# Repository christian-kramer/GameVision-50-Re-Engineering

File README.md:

# GameVision-50-Re-Engineering
Turning a bizarre Russian/Taiwanese NES clone into something useful.
___

I've been definitely been looking in strange places for personal projects to do, lately. During my search I stumbled upon an old all-in-one game console/controller I used to play with when I was young.

This project is a continuation and implementation of my [STM32F103C8T6-Familiarization repo](https://github.com/christian-kramer/STM32F103C8T6-Familiarization)

It's called the **GameVision 50**, presumably because it has 50 games.

Here is the full list of games, in case anyone recognizes one.

And, as an example, here's "Truck Race":

The games aren't exactly sophisticated... not quite the level of immersion I'm looking for. The wheel is nice, though. I wonder how hard it would be to adapt it for use with a PC?

Let's open it up and have a look.

Seems a lot less complicated than I thought it would be, actually. Let's take a closer look at that mainboard.

Interesting layout, for sure. The big chip on the right is almost certainly a parallel flash IC, the chip-on-board in the lower-left is probably the main game processor (more on that in a bit), and quite honestly I have no idea what the "chip-on-board, on-board" thing in the top left is. It's gotta be a coprocessor of some sort, because it's thoroughly interconnected with both the game chip, and the flash chip. A converter between parallel flash and whatever interface the game processor requires, perhaps?

I'm interested in that connector on the far right of the board. It definitely doesn't appear to be a multiplexed analog button arrangement... the pin names like "SCK1", "OUT0", and "VCC" seem to indicate we've got some other device at the other end of this cable speaking a serial data language. I have never heard of "OUT0" in any serial data protocol I've worked with.

I googled some of these pinout names, and the first result on Google was [this webpage](http://xn----ctbgeuhdtdb2b.xn--p1ai/price/dendy/?parts&d=DW-MH-3):

Woah! That's a lot of Russian. I can read some Russian, but not stuff that's this technical.

That's better. Looks like it's actually pretty straightforward. Dendy DW-MH-3? I've never heard of the company "Dendy Processors" before. I really want to know more about this chip.

Googling the company "Dendy Processors" led me to this Wikipedia page:

Holy cow! "Dendy" was actually a Soviet NES clone! This project just got *really* interesting. I guess technically now I'm reverse-engineering 80's-vintage Soviet tech.

This makes a lot of sense now, because studying the board more I notice the oscillator's frequency is very familiar:

The frequency indicated on this oscillator is 21.4772 MHz... Check out what we get when we google this frequency.

It's all NES/SNES stuff! Ha!

That last link is interesting, too. The *reason* 21.4772 MHz is used is because that's the sample rate for 525-line B-MAC video encoding.

70's/80's video encoding standards are absolutely fascinating, and I highly encourage you to explore this rabbit hole if you're interested. The Wikipedia article on B-MAC  is a great starting point with tons of links that will take you further.

Back to the project at hand! The Russian Dendy documentation page indicates VCC gets +5v, OUT0 is a common clock, SCK1 and SCK2 are clocks specific to each controller, and P1D0/P2D0 are the lines that the controllers transmit data on.

I've got a logic analyzer I can hook up to this and see if I can recognize a pattern.

Next, let's fire it up and press some buttons!

The top line is SCK1, and the next line down is P1D0. Looks like we've got a 2-byte "packet" clocked out by SCK1, with a little bit of a pause separating them. I'm curious, though... The webpage mentioned that OUT0 is a "common clock"... What does its output look like?

Ah, okay! OUT0 appears to delineate each byte. It also looks like no matter which button I press on the wheel, both bytes are identical. I wonder if this is some crude error-checking going on?

Also, interestingly enough, this output is from the wheel being turned all the way to the left, meaning that although there's a potentiometer attached to the steering column, there is no analog data coming back to the Dendy chip... turning the wheel is functionally equivalent to pressing the left or right d-pad buttons! This will need to be rewired if we want this to function as an analog axis.

At this point, I think I'm comfortable enough with the Dendy controller protocol to try hooking this up to an STM32 Blue Pill.

What you see here is the steering wheel controller of the GameVision 50 bypassing the original mainboard and communicating entirely with the STM32. Interestingly, it's able to interface directly with the STM32 without level-shifting because STM32 inputs are 5v tolerant, and 3.3v is above the TTL "logic high" threshold. The potentiometer on the breadboard is a stand-in for the one that's built-in to the steering column. I'll use that potentiometer in the final version.

After I got it talking with my PC and being recognized as a "Game Pad" in Windows with a single "steering" axis, it was time to take this rat's nest of wiring and turn it into a PCB!

I decided to keep the same shape and general layout as the original mainboard so that it may be a drop-in replacement/conversion. It felt much more professional, that way. Additionally, I broke out the steering wheel connector into test-points so that I may easily connect my logic analyzer in the event that I needed to debug my firmware in the future. The header for that is labeled J4, to the left of J5: the controller connector.

When the boards finally arrived, I was ecstatic about how they turned out! The "Gamevision" logo looks amazing, and all of the tiny capacitors and resistors were soldered perfectly. I opted to have the surface-mount components assembled at the factory due to the amount of fine-pitch soldering I would otherwise have to do myself. The only surface-mount component the factory couldn't do was the USB port, which was easy enough for me to hand-solder.

Here you can see my board (left) vs. the old board (right). You can see how similar they are physically, but it also really gives you an idea of just how much more component-dense the old board is compared to mine. Lots of analog signals going on over there!

Here's another comparison view showing how I incorporated the existing JST-XH-7 connector into my design. Because I retained the same connector in the same location, the wheel plugs right in like it was made for it!

Now, to tackle this empty shell. That potentiometer in the middle will need to be reworked in order to work the way I want it to. Let's take a closer look to see why.

Right now there's a big ol' glob of solder connecting the wiper pin with ground, making the potentiometer act like a variable resistor. This is then hooked up to the wheel's control board, which senses if the wheel is turned left or right, and registers a "left" or "right" button-press accordingly.

This doesn't work for what we want it to do! We want to measure *how far* the wheel is turned left or right, not "if". For that, we need to connect this potentiometer up to the  PCB directly so the STM32 can read the analog signal, and not the wheel. But, if we disconnect the potentiometer from the two wires and just leave them hanging, we'll forever get a "right" button press due to the infinite resistance!

We need to trick the wheel into thinking the potentiometer is always in the center. I measured 4.7KΩ across the potentiometer in the "center" positon, so an approximately 4.7KΩ fixed resistor soldered to the wires should be a perfect stand-in.

I had this resistor sitting in my "loose parts" bowl on my workbench. It measured something like 3.7KΩ, so close enough. After I soldered it on... no more "right" button press coming from the controller!

Lastly, here it is all assembled. I repurposed the 3-wire Audio/Video ribbon cable for the potentiometer, and it all works great! Steering is super smooth, and all of the buttons work!

I'm glad I incorporated the test-point pin header, next to the controller connector. Initially, during writing the firmware, I was getting some weird data I had never encountered before. When I pressed a button, my PC indicated many other buttons being pressed as well! To me, this looked like a timing issue... But I wasn't entirely sure where in my program the issue could be. Being able to easily connect a logic analyzer to inspect my signals allowed me to easily pinpoint the issue of "**P1D0**" not being pulled back up to +5V! This "floating" appeared as additional button presses to the STM32. Enabling the STM32's internal pull-up resistor on that pin in software allowed me to fix the issue without even needing a hardware fix.

After that, I closed it up and loaded up some games to try it out with!

Here is a video of me showing the wheel in action, playing Euro Truck Simulator 2:

[https://i.imgur.com/FMJOuTz.mp4](https://i.imgur.com/FMJOuTz.mp4)

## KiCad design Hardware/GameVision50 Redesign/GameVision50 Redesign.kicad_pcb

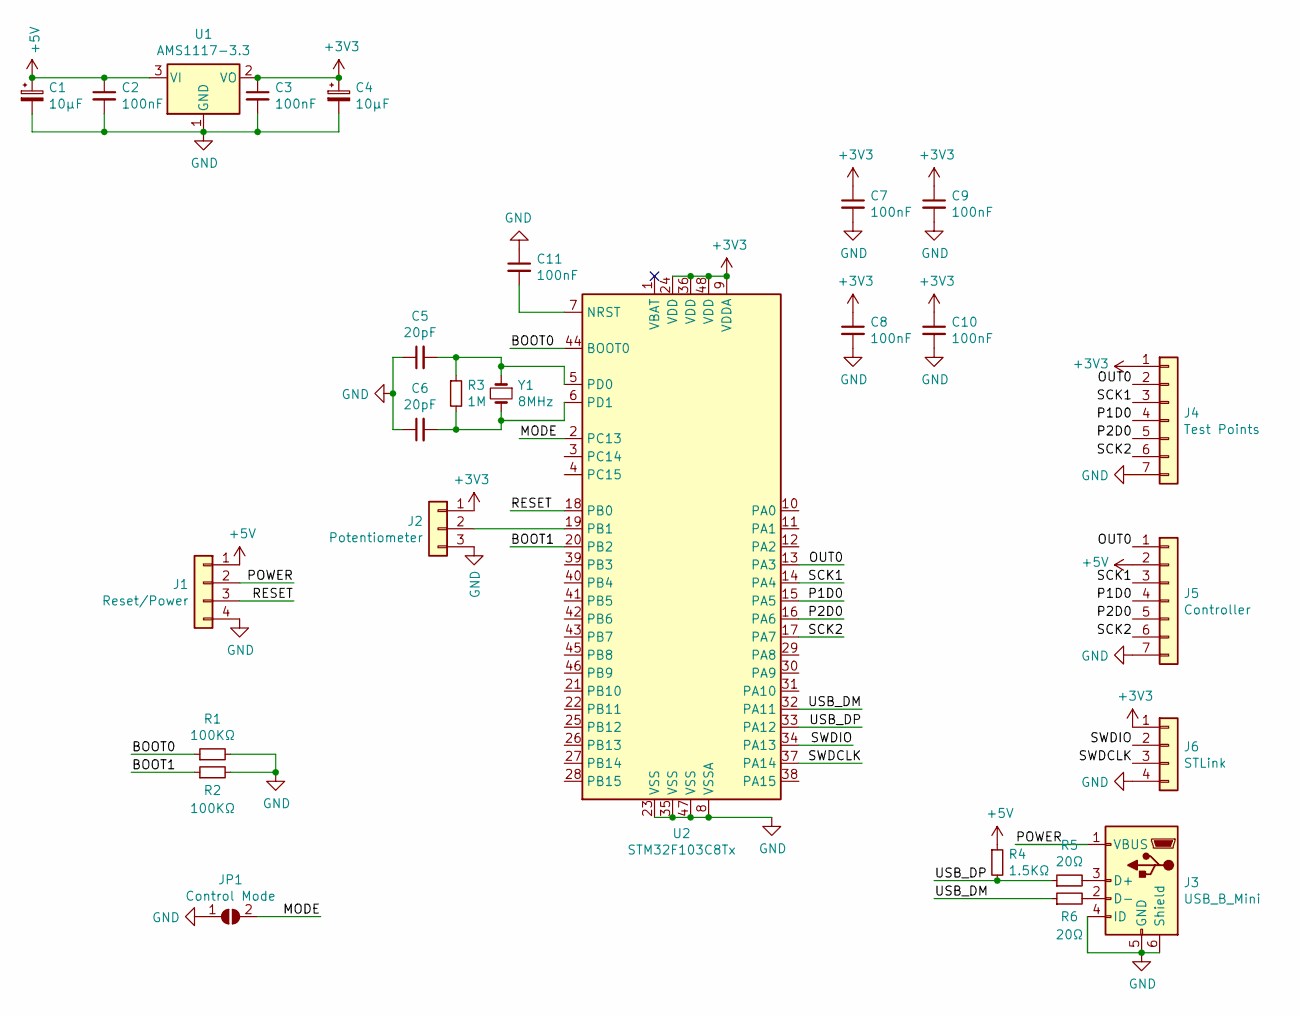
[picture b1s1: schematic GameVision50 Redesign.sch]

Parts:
C1, C4: 10μF; C_0805_2012Metric; LCSC C15850
C2, C3, C7, C8, C9, C10, C11: 100nF; C_0402_1005Metric; LCSC C1525
C5, C6: 20pF; C_0603_1608Metric; LCSC C1648
J1: Reset/Power; PinHeader_1x04_P2.54mm_Vertical
J2: Potentiometer; PinHeader_1x03_P2.54mm_Vertical
J3: USB_B_Mini; USB_Mini-B_Lumberg_2486_01_Horizontal
J4: Test Points; PinHeader_1x07_P2.54mm_Vertical
J5: Controller; JST_XH_B7B-XH-A_1x07_P2.50mm_Vertical
J6: STLink; PinHeader_1x04_P2.54mm_Vertical
JP1: Control Mode; SolderJumper-2_P1.3mm_Open_TrianglePad1.0x1.5mm
R1, R2: 100KΩ; R_0402_1005Metric; LCSC C25741
R3: 1M; R_0402_1005Metric; LCSC C26083
R4: 1.5KΩ; R_0402_1005Metric; LCSC C25867
R5, R6: 20Ω; R_0603_1608Metric; LCSC C22950
U1: AMS1117-3.3; SOT-223-3_TabPin2; LCSC C6186
U2: STM32F103C8Tx; LQFP-48_7x7mm_P0.5mm; LCSC C8734
Y1: 8MHz; Crystal_SMD_5032-2Pin_5.0x3.2mm; LCSC C115962

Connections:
+3V3: C3.1, C4.1, C7.1, C8.1, C9.1, C10.1, J2.1, J4.1, J6.1, U1.2 (VO), U2.9 (VDDA), U2.24 (VDD), U2.36 (VDD), U2.48 (VDD)
+5V: C1.1, C2.1, J1.1, J5.2, R4.1, U1.3 (VI)
/BOOT0: R1.1, U2.44 (BOOT0)
/BOOT1: R2.1, U2.20 (PB2)
/MODE: JP1.2 (B), U2.2 (PC13)
/OUT0: J4.2, J5.1, U2.13 (PA3)
/P1D0: J4.4, J5.4, U2.15 (PA5)
/P2D0: J4.5, J5.5, U2.16 (PA6)
/POWER: J1.2, J3.1 (VBUS)
/RESET: J1.3, U2.18 (PB0)
/SCK1: J4.3, J5.3, U2.14 (PA4)
/SCK2: J4.6, J5.6, U2.17 (PA7)
/SWDCLK: J6.3, U2.37 (PA14)
/SWDIO: J6.2, U2.34 (PA13)
/USB_DM: R6.1, U2.32 (PA11)
/USB_DP: R4.2, R5.1, U2.33 (PA12)
GND: C1.2, C2.2, C3.2, C4.2, C5.1, C6.1, C7.2, C8.2, C9.2, C10.2, C11.1, J1.4, J2.3, J3.4 (ID), J3.5 (GND), J3.6 (Shield), J4.7, J5.7, J6.4, JP1.1 (A), R1.2, R2.2, U1.1 (GND), U2.8 (VSSA), U2.23 (VSS), U2.35 (VSS), U2.47 (VSS)
unnamed: C5.2, R3.1, U2.5 (PD0), Y1.1
unnamed: C6.2, R3.2, U2.6 (PD1), Y1.2
unnamed: C11.2, U2.7 (NRST)
unnamed: J2.2, U2.19 (PB1)
unnamed: J3.2 (D-), R6.2
unnamed: J3.3 (D+), R5.2

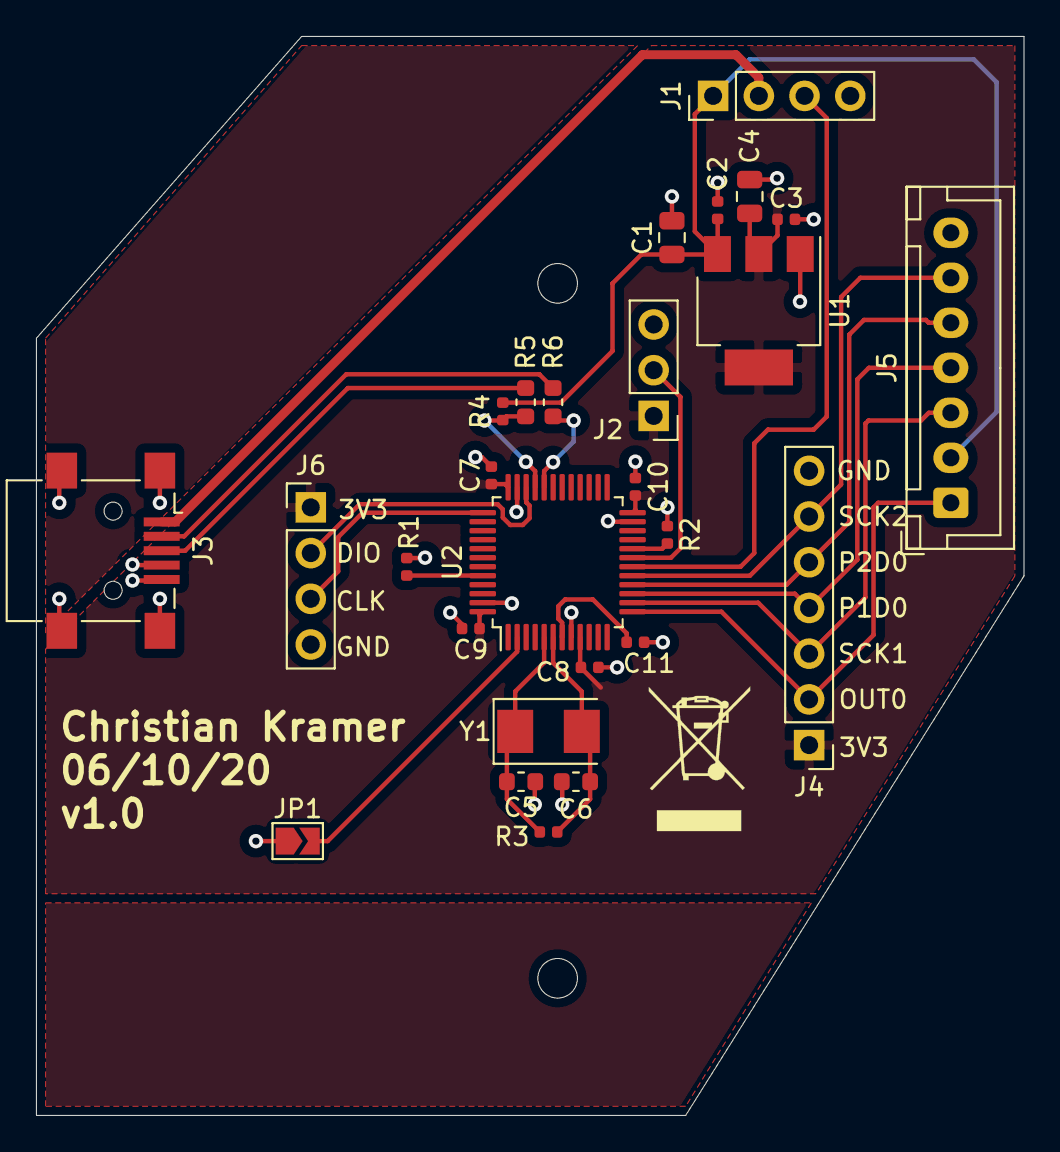
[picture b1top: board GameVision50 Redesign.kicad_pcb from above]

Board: 2 copper layers, 54.9 x 59.9 mm, 27 parts (0 on the bottom side), 23 nets.

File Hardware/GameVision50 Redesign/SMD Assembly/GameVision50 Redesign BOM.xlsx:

Comment | Designator | Footprint | LCSC
10μF | C1,C4 | Capacitor_SMD:C_0805_2012Metric | C15850
20pF | C5,C6 | Capacitor_SMD:C_0603_1608Metric | C1648
100nF | C7,C9,C8,C10,C2,C3,C11 | Capacitor_SMD:C_0402_1005Metric | C1525
Reset/Power | J1 | Connector_PinHeader_2.54mm:PinHeader_1x04_P2.54mm_Vertical
Potentiometer | J2 | Connector_PinHeader_2.54mm:PinHeader_1x03_P2.54mm_Vertical
USB_B_Mini | J3 | Connector_USB:USB_Mini-B_Lumberg_2486_01_Horizontal
Test Points | J4 | Connector_PinHeader_2.54mm:PinHeader_1x07_P2.54mm_Vertical
Controller | J5 | Connector_JST:JST_XH_B7B-XH-A_1x07_P2.50mm_Vertical
STLink | J6 | Connector_PinHeader_2.54mm:PinHeader_1x04_P2.54mm_Vertical
Control Mode | JP1 | Jumper:SolderJumper-2_P1.3mm_Open_TrianglePad1.0x1.5mm
100KΩ | R1,R2 | Resistor_SMD:R_0402_1005Metric | C25741
1M | R3 | Resistor_SMD:R_0402_1005Metric | C26083
1.5KΩ | R4 | Resistor_SMD:R_0402_1005Metric | C25867
20Ω | R5,R6 | Resistor_SMD:R_0603_1608Metric | C22950
AMS1117-3.3 | U1 | Package_TO_SOT_SMD:SOT-223-3_TabPin2 | C6186
STM32F103C8Tx | U2 | Package_QFP:LQFP-48_7x7mm_P0.5mm | C8734
8MHz | Y1 | Crystal:Crystal_SMD_5032-2Pin_5.0x3.2mm | C115962

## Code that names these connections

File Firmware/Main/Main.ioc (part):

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Mcu.Name=STM32F103C(8-B)Tx
Mcu.Package=LQFP48
Mcu.UserName=STM32F103C8Tx
PA11.Mode=Device
PA11.Signal=USB_DM
PA12.Mode=Device
PA12.Signal=USB_DP
PA13.Mode=Serial_Wire
PA13.Signal=SYS_JTMS-SWDIO
PA14.Mode=Serial_Wire
PA14.Signal=SYS_JTCK-SWCLK
PA3.GPIOParameters=GPIO_Label
PA3.GPIO_Label=Global_Clock
PA3.Signal=GPIO_Output
PA4.GPIOParameters=GPIO_Label
PA4.GPIO_Label=Controller_Clock
PA4.Signal=GPIO_Output
PA5.GPIOParameters=GPIO_PuPd,GPIO_Label
PA5.GPIO_Label=Controller_Data
PA5.GPIO_PuPd=GPIO_PULLUP
PA5.Signal=GPIO_Input
PA6.GPIOParameters=GPIO_Label
PA6.GPIO_Label=P2D0
PA6.Signal=GPIO_Input
PA7.GPIOParameters=GPIO_Label
PA7.GPIO_Label=SCK2
PA7.Signal=GPIO_Output
PB0.GPIOParameters=GPIO_PuPd,GPIO_Label
PB0.GPIO_Label=RESET
PB0.GPIO_PuPd=GPIO_PULLUP
PB0.Signal=GPIO_Input
PB1.Signal=ADCx_IN9
PC13-TAMPER-RTC.GPIOParameters=GPIO_Label
PC13-TAMPER-RTC.GPIO_Label=Mode
PC13-TAMPER-RTC.Signal=GPIO_Input
PD0-OSC_IN.Mode=HSE-External-Oscillator
PD0-OSC_IN.Signal=RCC_OSC_IN
PD1-OSC_OUT.Mode=HSE-External-Oscillator
PD1-OSC_OUT.Signal=RCC_OSC_OUT
RCC.SYSCLKFreq_VALUE=72000000
RCC.SYSCLKSource=RCC_SYSCLKSOURCE_PLLCLK
board=custom

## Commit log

2020-06-01 working steering and 16-button interface
2020-06-01 limited 16 button interface to 13 buttons
2020-06-02 changed to rely on siezeof instead of manual total
2020-06-02 Updated USB HID MID/PID
2020-06-02 working interface with PC with left thumb button
2020-06-03 fast, reliable working buttons and steering
2020-06-05 first version of kicad schematic prior to annotate
2020-06-05 annotated and assigned footprints
2020-06-05 added power-on reset IC with pull-up and bypass cap
2020-06-05 made edge cuts and mounting holes
2020-06-08 better footprint layout and 3d model of oscillator
2020-06-11 exported version 1 of PCB to manufacture
2020-06-11 created main firmware project for compatibility
2020-06-24 Adjusted vertical image sizes
2020-06-24 Reworked bug-chasing paragraph
2020-07-18 updated to reflect current state of project
